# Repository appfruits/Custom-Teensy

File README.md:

# Custom-Teensy
This is a reference pcb and schematics for a custom Teensy 3.1 board in EAGLE CAD format. More info on this can be found in our blog post at: http://www.appfruits.com/2015/03/building-your-own-custom-teensy/

#Wiki
Please post an issue if you have trouble or questions on the design. I will add new interesting things that I found in the issues and other sources (like PJRCs official forum or from eMail conversations) to the Wiki of this project. You are kindly invited to add things, too.
https://github.com/appfruits/Custom-Teensy/wiki

## License
<br /><span xmlns:dct="http://purl.org/dc/terms/" property="dct:title">Custom Teensy 3.1</span> von <a xmlns:cc="http://creativecommons.org/ns#" href="http://www.appfruits.com/2015/03/building-your-own-custom-teensy/" property="cc:attributionName" rel="cc:attributionURL">Phillip Schuster (Appfruits)</a> ist lizenziert unter einer <a rel="license" href="http://creativecommons.org/licenses/by-sa/4.0/">Creative Commons Namensnennung - Weitergabe unter gleichen Bedingungen 4.0 International Lizenz</a>.<br />Beruht auf dem Werk unter <a xmlns:dct="http://purl.org/dc/terms/" href="https://www.pjrc.com/store/teensy31.html" rel="dct:source">https://www.pjrc.com/store/teensy31.html</a>.

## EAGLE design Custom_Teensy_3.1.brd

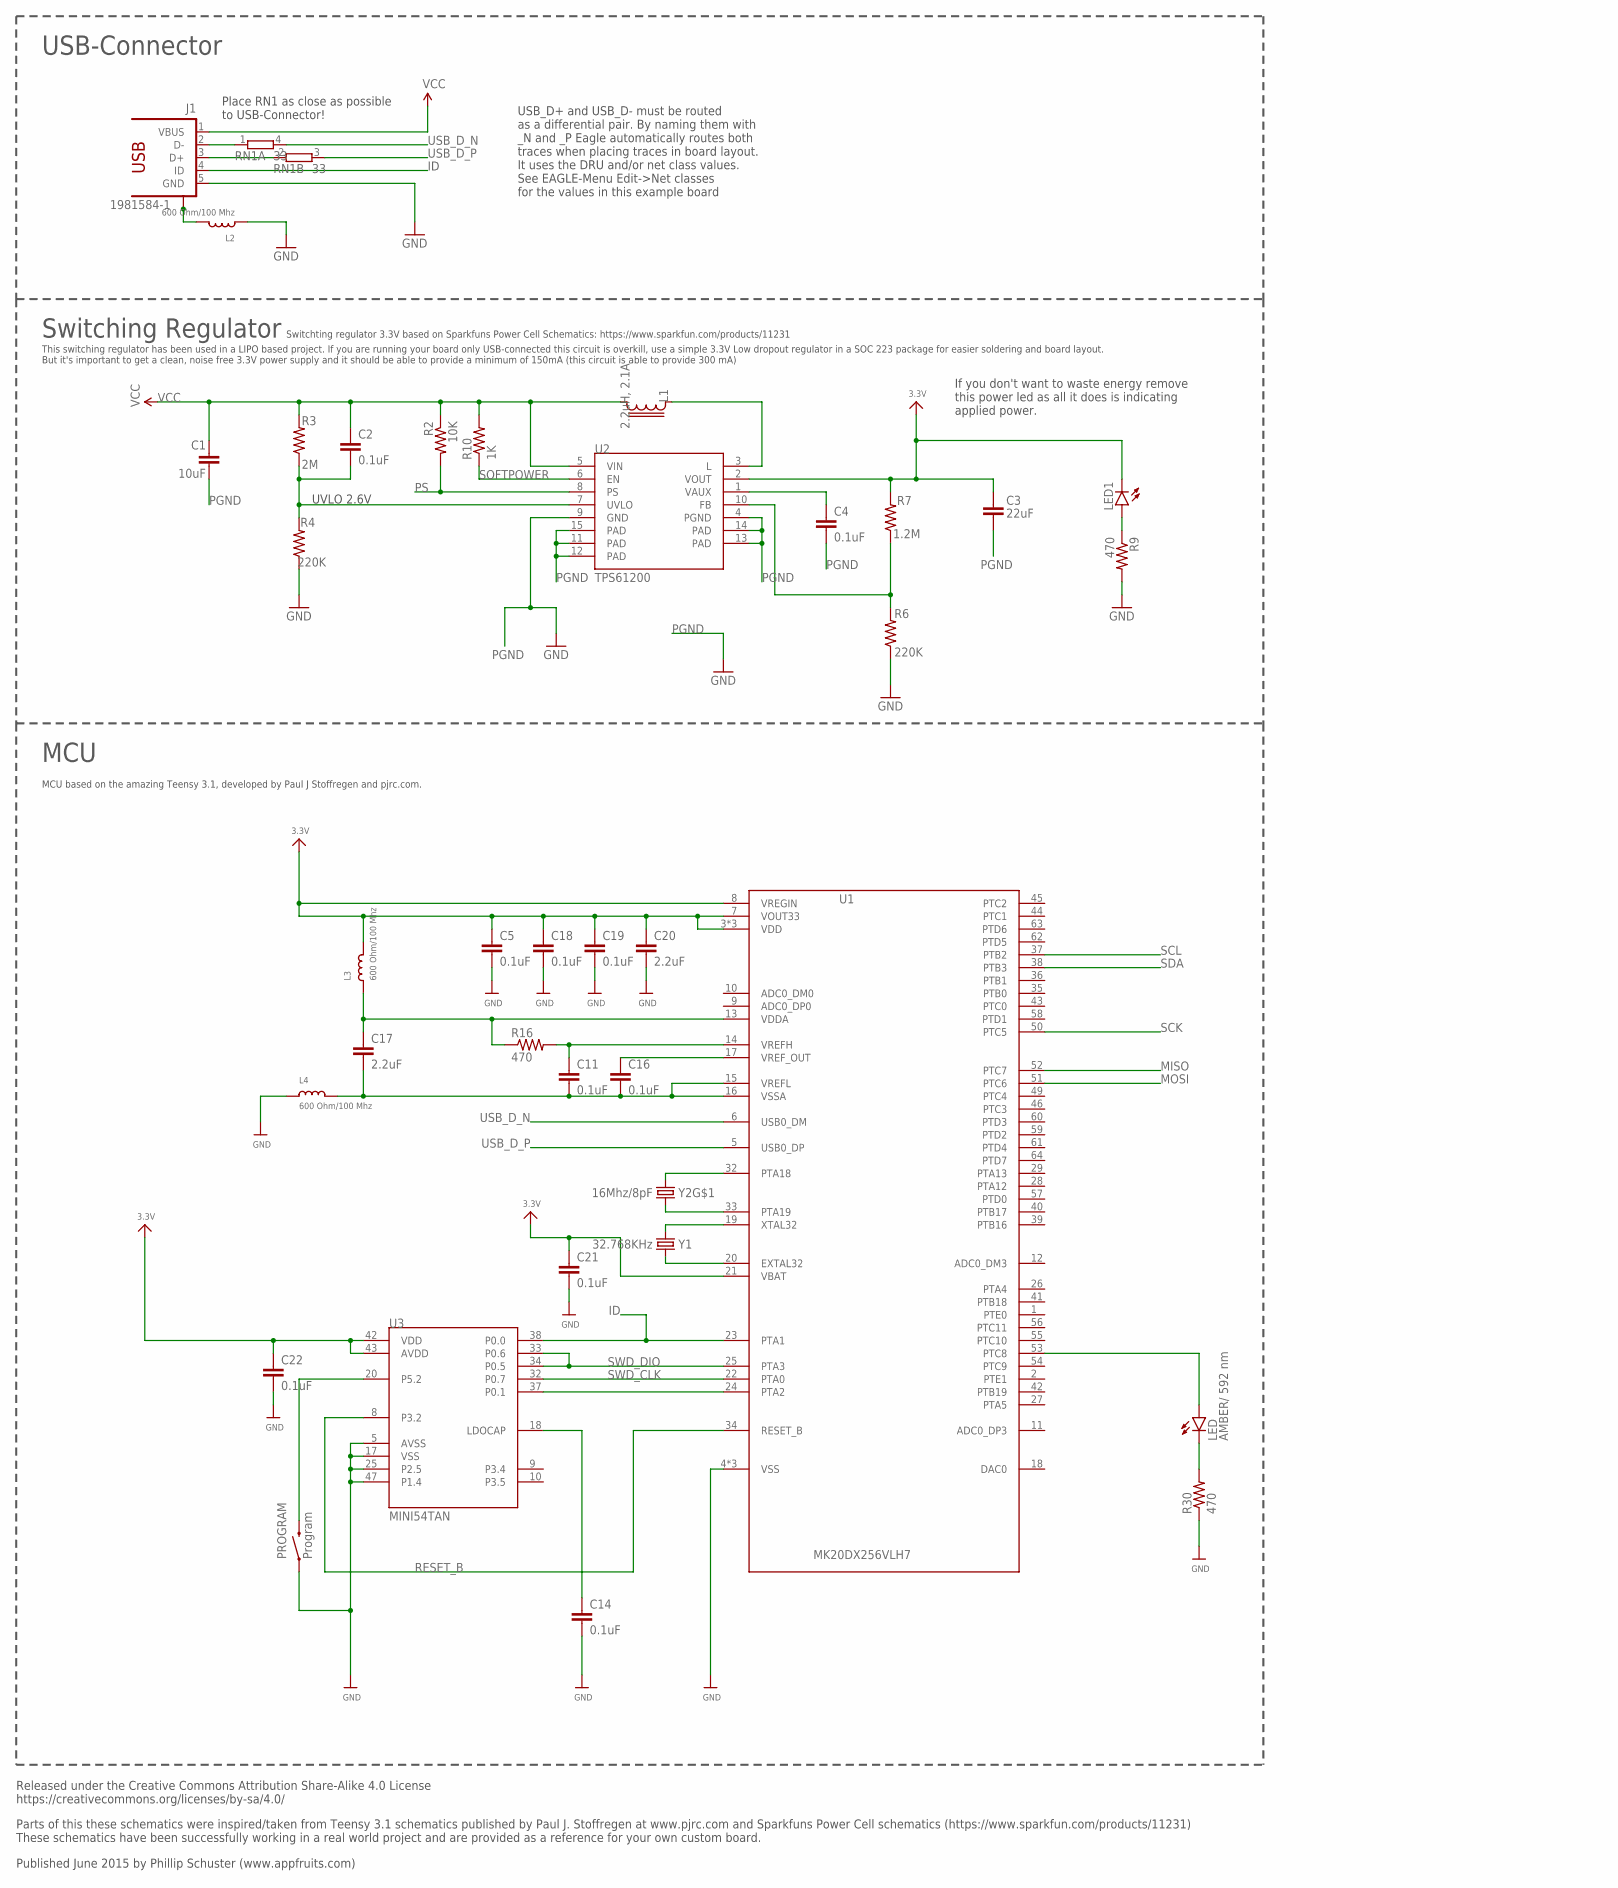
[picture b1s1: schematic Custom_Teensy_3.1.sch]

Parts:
C1: 10uF; 0603-CAP
C2, C4, C5, C11, C14, C16, C18, C19, C21, C22: 0.1uF; 0603-CAP
C3: 22uF; 0603-CAP
C17, C20: 2.2uF; 0603-CAP
J1: 1981584-1; MPN ZX62-AB-5PA(11)
L1: 2.2uH, 2.1A; LPS3015
L2, L3, L4: 600 Ohm/100 Mhz; 0805
LED: AMBER/ 592 nm; LED-0603
LED1: LED-GREEN; LED-0603
PROGRAM: Program; TACTILE-SWITCH-1101NE; MPN RS-282G05A3-SM RT
R2: 10K; 0603-RES
R3: 2M; 0603-RES
R4, R6: 220K; 0603-RES
R7: 1.2M; 0603-RES
R9, R16, R30: 470; 0603-RES
R10: 1K; 0603-RES
RN1: 33; EXB34V; MPN EXB-34V330JV
U1: MK20DX256VLH7; MPN MK20DX256VLH7
U2: TPS61200; QFN-10_PAD
U3: MINI54TAN
Y1: 32.768KHz; CRYSTAL-TXC-7A; MPN FC-255 32.7680K-A3
Y2: 16Mhz/8pF; CRYSTAL-SMD-5X3; MPN ECS-160-8-30B-CKM

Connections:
3.3V: C3.1, C5.1, C18.1, C19.1, C20.1, C21.1, C22.1, L3.2, LED1.C, R7.2, U1.3 (VDD), U1.7 (VOUT33), U1.8 (VREGIN), U1.21 (VBAT), U1.30 (VDD), U1.48 (VDD), U2.2 (VOUT), U3.42 (VDD), U3.43 (AVDD)
FB: R6.2, R7.1, U2.10 (FB)
GND: C5.2, C14.2, C18.2, C19.2, C20.2, C21.2, C22.2, J1.5 (GND), L2.1, L4.1, PROGRAM.P$1 (1), R4.1, R6.1, R9.2, R30.1, U1.4 (VSS), U1.31 (VSS), U1.47 (VSS), U3.5 (AVSS), U3.17 (VSS), U3.25 (P2.5), U3.47 (P1.4)
ID: J1.4 (ID), U1.23 (PTA1), U3.38 (P0.0)
MISO: U1.52 (PTC7)
MOSI: U1.51 (PTC6)
unnamed: LED1.A, R9.1
unnamed: L1.1, U2.3 (L)
unnamed: LED.A, U1.53 (PTC8)
unnamed: U1.24 (PTA2), U3.37 (P0.1)
unnamed: LED.C, R30.2
unnamed: PROGRAM.P$2 (2), U3.20 (P5.2)
unnamed: C14.1, U3.18 (LDOCAP)
unnamed: U1.32 (PTA18), Y2.3 (2)
unnamed: U1.33 (PTA19), Y2.1
unnamed: U1.19 (XTAL32), Y1.P$2 (2)
unnamed: U1.20 (EXTAL32), Y1.P$1 (1)
PGND: C1.2, C3.2, C4.2, U2.4 (PGND), U2.9 (GND), U2.11 (PAD), U2.12 (PAD), U2.13 (PAD), U2.14 (PAD), U2.15 (PAD)
PS: R2.2, U2.8 (PS)
RESET_B: U1.34 (RESET_B), U3.8 (P3.2)
SCK: U1.50 (PTC5)
SCL: U1.37 (PTB2)
SDA: U1.38 (PTB3)
SOFTPOWER: R10.1, U2.6 (EN)
SWD_CLK: U1.22 (PTA0), U3.32 (P0.7)
SWD_DIO: U1.25 (PTA3), U3.33 (P0.6), U3.34 (P0.5)
USB_CON_N: J1.2 (D-), RN1.1
USB_CON_P: J1.3 (D+), RN1.2 (1)
USB_D_N: RN1.4 (2), U1.6 (USB0_DM)
USB_D_P: RN1.3 (2), U1.5 (USB0_DP)
USB_SHIELD: J1.S1, J1.S2, J1.S3, J1.S4, L2.2
UVLO: C2.2, R3.1, R4.2, U2.7 (UVLO)
VAUX: C4.1, U2.1 (VAUX)
VCC: C1.1, C2.1, J1.1 (VBUS), L1.2, R2.1, R3.2, R10.2, U2.5 (VIN)
VDDA: C17.1, L3.1, R16.1, U1.13 (VDDA)
VREFH: C11.1, R16.2, U1.14 (VREFH)
VREFL: C11.2, C16.2, C17.2, L4.2, U1.15 (VREFL), U1.16 (VSSA)
VREF_OUT: C16.1, U1.17 (VREF_OUT)

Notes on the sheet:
UVLO 2.6V
USB-Connector
Switching Regulator
MCU
MCU based on the amazing Teensy 3.1, developed by Paul J Stoffregen and pjrc.com.
Place RN1 as close as possible to USB-Connector!
If you don't want to waste energy remove this power led as all it does is indicating applied power.
USB_D+ and USB_D- must be routed as a differential pair. By naming them with _N and _P Eagle automatically routes both traces when placing traces in board layout. It uses the DRU and/or net class values. See EAGLE-Menu Edit->Net classes for the values in this example board
Released under the Creative Commons Attribution Share-Alike 4.0 License https://creativecommons.org/licenses/by-sa/4.0/
Parts of this these schematics were inspired/taken from Teensy 3.1 schematics published by Paul J. Stoffregen at www.pjrc.com and Sparkfuns Power Cell schematics (https://www.sparkfun.com/products/11231) These schematics have been successfully working in a real world project and are provided as a r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
Published June 2015 by Phillip Schuster (www.appfruits.com)
Switchting regulator 3.3V based on Sparkfuns Power Cell Schematics: https://www.sparkfun.com/products/11231
This switching regulator has been used in a LIPO based project. If you are running your board only USB-connected this circuit is overkill, use a simple 3.3V Low dropout regulator in a SOC 223 package for easier soldering and board layout. But it's important to get a clean, noise free 3.3V power sup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

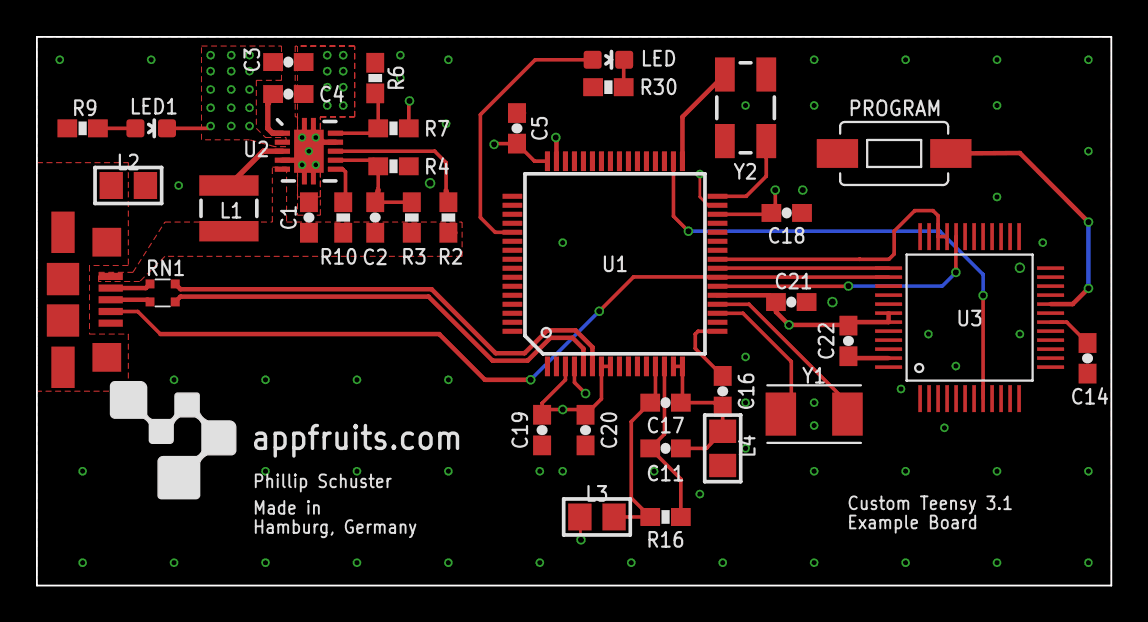
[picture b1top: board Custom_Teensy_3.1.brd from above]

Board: 4 copper layers, 59.7 x 30.5 mm, 37 parts (0 on the bottom side), 33 nets.

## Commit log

2015-06-26 Added License
2015-06-26 Added board and schematics
2015-06-26 Added an info to the Wiki on this repository
2015-06-26 Removed the I2C connection between MINI54TAN and MK20 as these are not used
    As this connection is shown in the official Teensy 3.1 schematics I
    have also added it. Paul today stated in the official PJRC forum that
    this connection is not used and will never be used. So I removed it.
2015-06-30 Added PDF for schematics and BOM for those that do not use EAGLE CAD
2016-03-22 fixed csv file for reader compatibility

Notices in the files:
README.md:
Creative Commons Lizenzvertrag
Custom_Teensy_3.1.brd:
to use/see all necessary layers. EAGLEs hobbyist license will do the trick.
parts and their libraries:
SparkFun-Electromechanical: Licensing: Creative Commons ShareAlike 4.0 International - https://creativecommons.org/licenses/by-sa/4.0
con-usb: Copyright (C) 2008, Bob Starr
